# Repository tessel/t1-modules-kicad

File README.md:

**[UNMAINTAINED] This library does not have a maintainer. The source code and repository will be kept at this URL indefinitely. If you'd like to help maintain this codebase, create an issue on this repo explaining why you'd like to become a maintainer and tag @tessel/maintainers in the body.**

# t1-modules-kicad

## libraries

sources:

* `library/tessel.pretty/QFN-*` &mdash; <https://github.com/KiCad/Housings_DFN_QFN.pretty>
* `library/freescale-ic.dcm` &mdash; <https://github.com/mcous/kicad-lib>

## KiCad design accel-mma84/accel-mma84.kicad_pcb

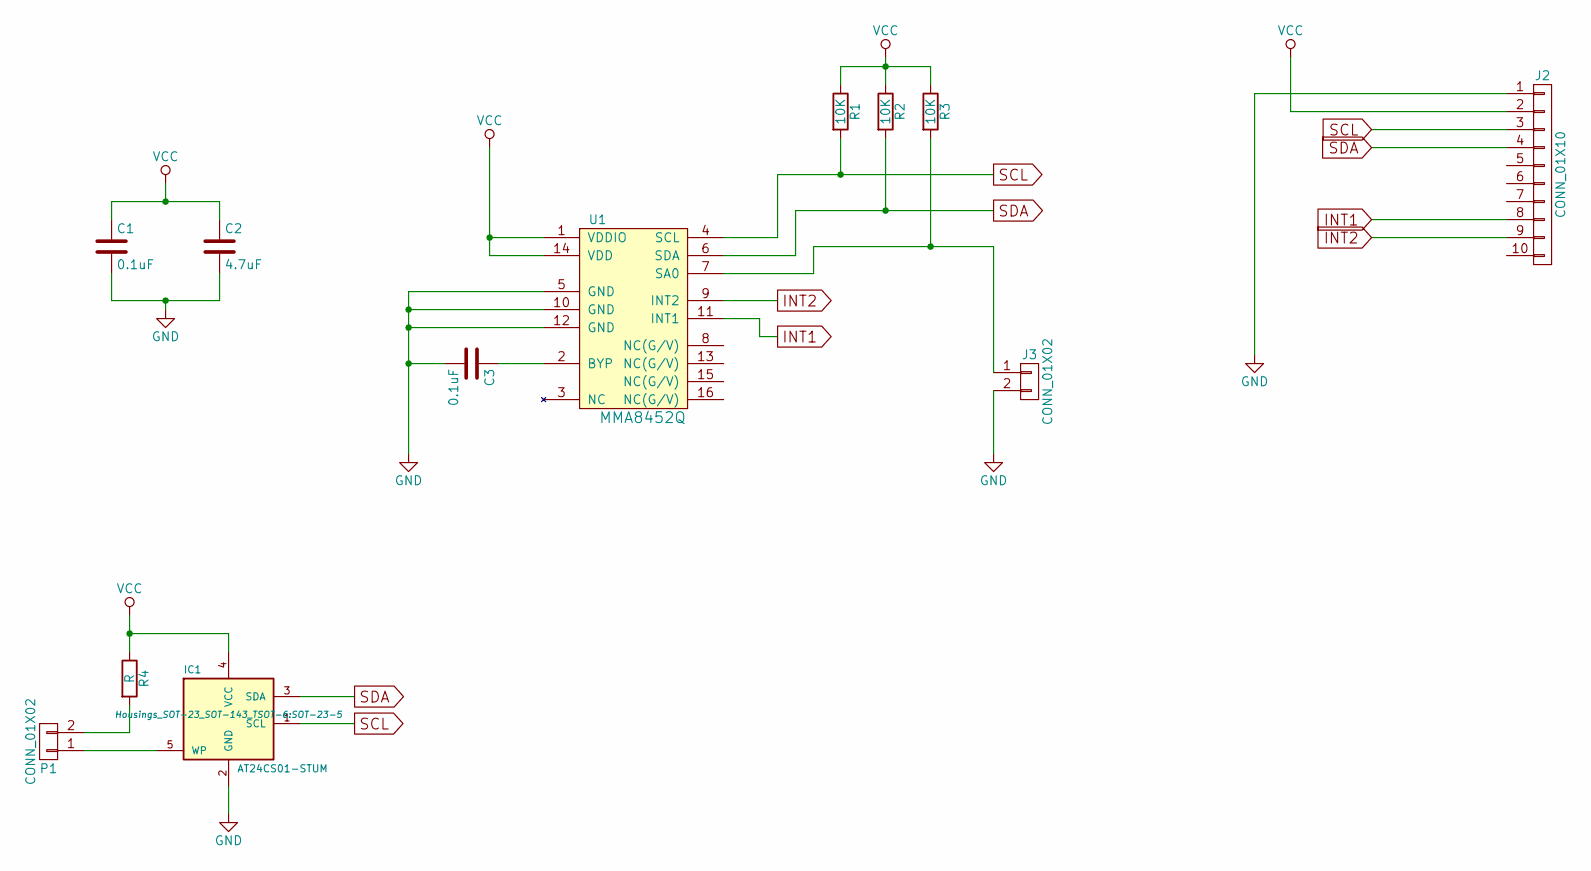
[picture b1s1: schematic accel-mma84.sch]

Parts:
C1, C3: 0.1uF; C_0603
C2: 4.7uF; C_0603
IC1: AT24CS01-STUM; SOT-23-5
J2: CONN_01X10; Socket_Strip_Angled_1x10
J3: CONN_01X02; Socket_Strip_Straight_1x02
P1: CONN_01X02; Socket_Strip_Straight_1x02
R1, R2, R3: 10K; R_0603
R4: R; R_0603
U1: MMA8452Q; QFN-16-1EP_3x3mm_Pitch0.5mm

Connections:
GND: C1.2, C2.2, C3.2, IC1.2 (GND), J2.1, J3.2, U1.5 (GND), U1.10 (GND), U1.12 (GND)
INT1: J2.8, U1.11 (INT1)
INT2: J2.9, U1.9 (INT2)
unnamed: C3.1, U1.2 (BYP)
unnamed: IC1.5 (WP), P1.1
unnamed: J3.1, R3.2, U1.7 (SA0)
unnamed: P1.2, R4.2
SCL: IC1.1 (SCL), J2.3, R1.2, U1.4 (SCL)
SDA: IC1.3 (SDA), J2.4, R2.2, U1.6 (SDA)
VCC: C1.1, C2.1, IC1.4 (VCC), J2.2, R1.1, R2.1, R3.1, R4.1, U1.1 (VDDIO), U1.14 (VDD)

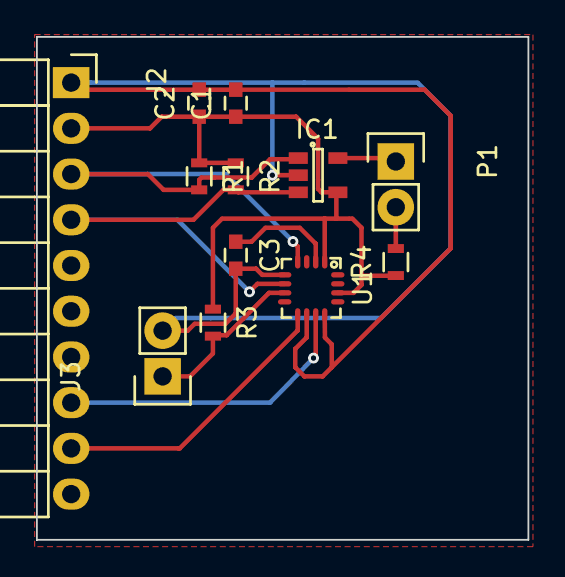
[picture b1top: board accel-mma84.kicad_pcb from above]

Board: 2 copper layers, 27.3 x 27.9 mm, 12 parts (0 on the bottom side), 10 nets.

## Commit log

2015-07-04 Initial commit for Accel.
2015-07-05 Adds initial accelerometer draft.
2015-07-05 Reduces via count.
2015-07-06 Reorganizes component layout.
2015-07-08 Reorganizes files, extracts libraries.
2015-07-08 Adds README.
2015-07-08 Moves accelerometer data into its own folder.
2015-07-18 Adds a bridge for disabling write protection.
2015-07-18 Updates footprint
2015-07-21 Corrects trace widths.
2016-08-23 Adds unmaintained notice
